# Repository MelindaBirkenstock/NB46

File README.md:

# NB47
 NB47 Mechanical keyboard, supports MX
probably doesn't work no promises

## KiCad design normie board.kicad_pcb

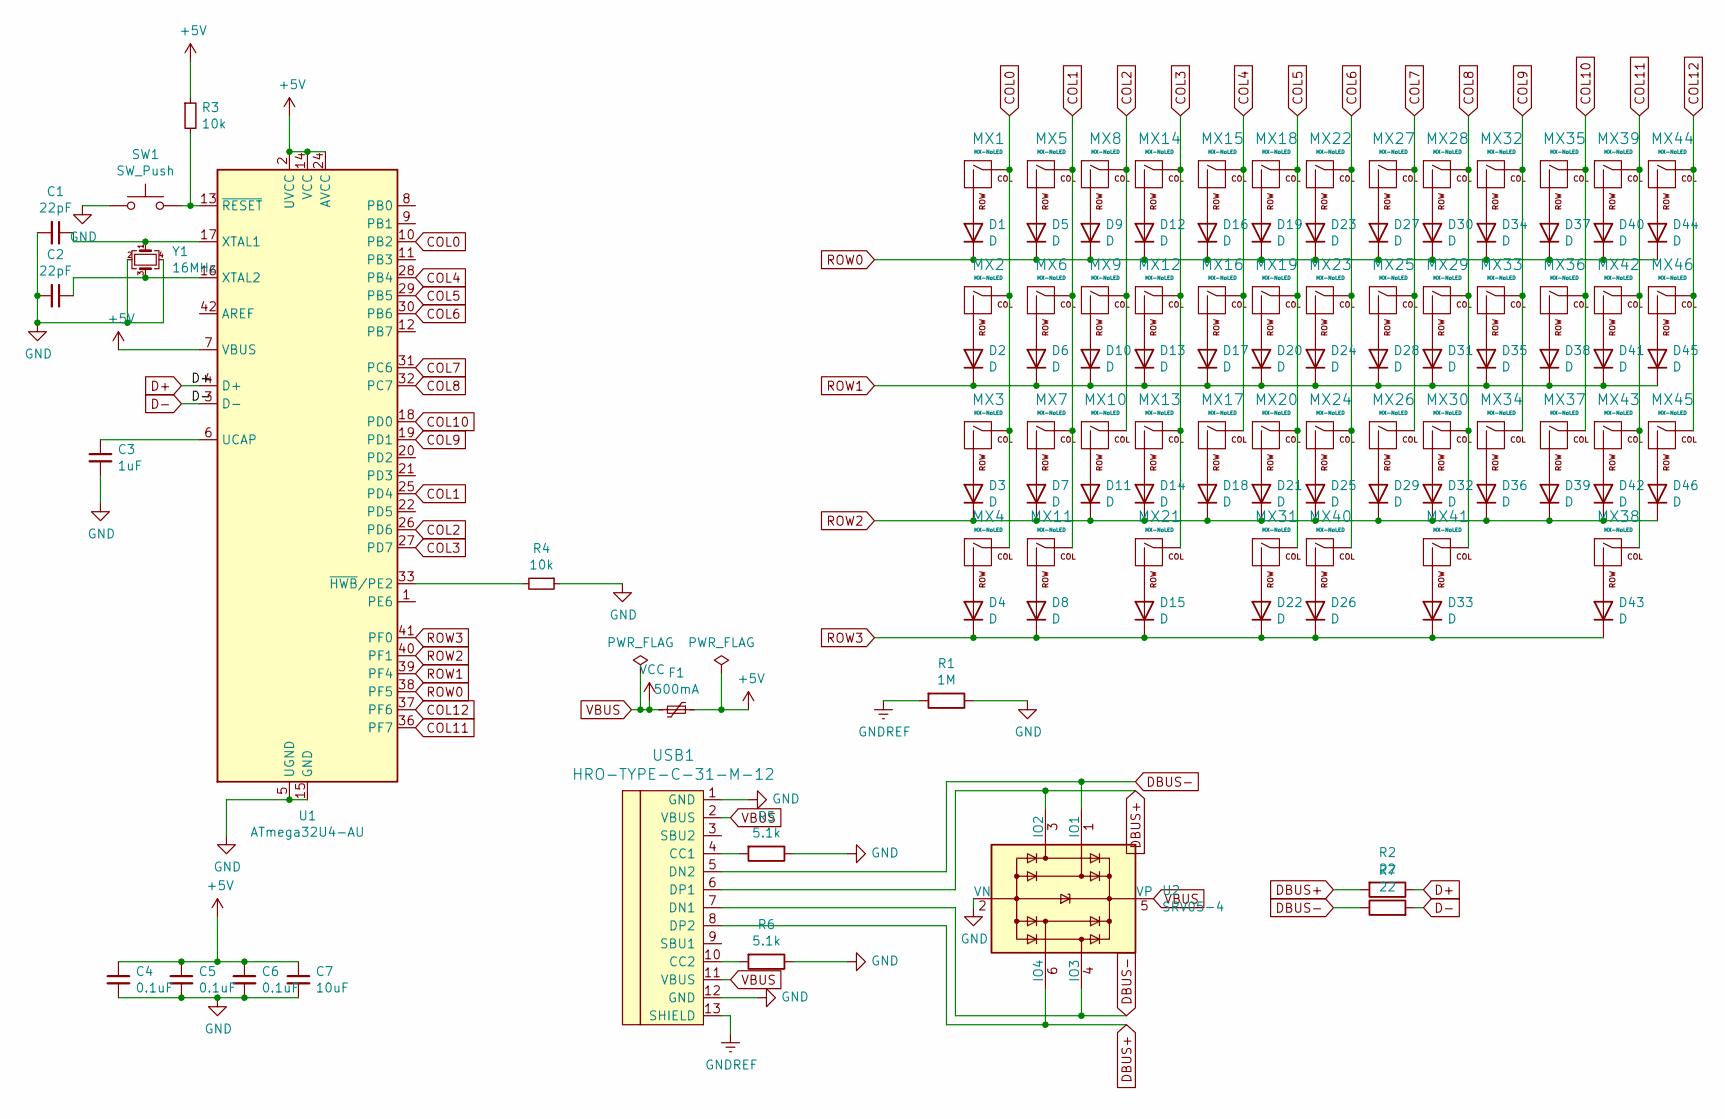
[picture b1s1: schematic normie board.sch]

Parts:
C1, C2: 22pF; C_0805_2012Metric_Pad1.15x1.40mm_HandSolder
C3: 1uF; C_0805_2012Metric_Pad1.15x1.40mm_HandSolder
C4, C5, C6: 0.1uF; C_0805_2012Metric_Pad1.15x1.40mm_HandSolder
C7: 10uF; C_0805_2012Metric_Pad1.15x1.40mm_HandSolder
D1, D2, D3, D4, D5, D6, D7, D8, D9, D10, D11, D12, D13, D14, D15, D16, D17, D18, D19, D20, D21, D22, D23, D24, D25, D26, D27, D28, D29, D30, D31, D32, D33, D34, D35, D36, D37, D38, D39, D40, D41, D42, D43, D44, D45, D46: D; D_0805_2012Metric_Pad1.15x1.40mm_HandSolder
F1: 500mA; Fuse_1206_3216Metric_Pad1.42x1.75mm_HandSolder
MX1, MX4, MX38, MX39, MX43: MX-NoLED; SW_Cherry_MX_1.50u_PCB
MX2, MX42: MX-NoLED; SW_Cherry_MX_1.75u_PCB
MX3, MX21: MX-NoLED; SW_Cherry_MX_2.25u_PCB
MX5, MX6, MX7, MX8, MX9, MX10, MX12, MX13, MX14, MX15, MX16, MX17, MX18, MX19, MX20, MX22, MX23, MX24, MX25, MX26, MX27, MX28, MX29, MX30, MX31, MX32, MX33, MX34, MX35, MX36, MX37, MX44, MX45, MX46: MX-NoLED; SW_Cherry_MX_1.00u_PCB
MX11, MX41: MX-NoLED; SW_Cherry_MX_1.25u_PCB
MX40: MX-NoLED; SW_Cherry_MX_2.75u_PCB
R1: 1M; R_0805_2012Metric_Pad1.15x1.40mm_HandSolder
R2, R7: 22; R_0805_2012Metric_Pad1.15x1.40mm_HandSolder
R3, R4: 10k; R_0805_2012Metric_Pad1.15x1.40mm_HandSolder
R5, R6: 5.1k; R_0805_2012Metric_Pad1.15x1.40mm_HandSolder
SW1: SW_Push; PinHeader_1x02_P2.54mm_Horizontal
U1: ATmega32U4-AU; TQFP-44_10x10mm_P0.8mm
U2: SRV05-4; SOT-23-6
USB1: HRO-TYPE-C-31-M-12; HRO-TYPE-C-31-M-12-HandSoldering
Y1: 16MHz; Crystal_SMD_3225-4Pin_3.2x2.5mm

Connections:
+5V: C4.1, C5.1, C6.1, C7.1, F1.1, R3.1, U1.2 (UVCC), U1.7 (VBUS), U1.14 (VCC), U1.24 (AVCC), U1.34 (VCC), U1.44 (AVCC)
COL0: MX1.1 (COL), MX2.1 (COL), MX3.1 (COL), MX4.1 (COL), U1.10 (PB2)
COL1: MX5.1 (COL), MX6.1 (COL), MX7.1 (COL), MX11.1 (COL), U1.25 (PD4)
COL2: MX8.1 (COL), MX9.1 (COL), MX10.1 (COL), U1.26 (PD6)
COL3: MX12.1 (COL), MX13.1 (COL), MX14.1 (COL), MX21.1 (COL), U1.27 (PD7)
COL4: MX15.1 (COL), MX16.1 (COL), MX17.1 (COL), U1.28 (PB4)
COL5: MX18.1 (COL), MX19.1 (COL), MX20.1 (COL), MX31.1 (COL), U1.29 (PB5)
COL6: MX22.1 (COL), MX23.1 (COL), MX24.1 (COL), MX40.1 (COL), U1.30 (PB6)
COL7: MX25.1 (COL), MX26.1 (COL), MX27.1 (COL), U1.31 (PC6)
COL8: MX28.1 (COL), MX29.1 (COL), MX30.1 (COL), MX41.1 (COL), U1.32 (PC7)
COL9: MX32.1 (COL), MX33.1 (COL), MX34.1 (COL), U1.19 (PD1)
COL10: MX35.1 (COL), MX36.1 (COL), MX37.1 (COL), U1.18 (PD0)
COL11: MX38.1 (COL), MX39.1 (COL), MX42.1 (COL), MX43.1 (COL), U1.36 (PF7)
COL12: MX44.1 (COL), MX45.1 (COL), MX46.1 (COL), U1.37 (PF6)
D+: R2.1, U1.4 (D+)
D-: R7.2, U1.3 (D-)
DBUS+: R2.2, U2.3 (IO2), U2.6 (IO4), USB1.6 (DP1), USB1.8 (DP2)
DBUS-: R7.1, U2.1 (IO1), U2.4 (IO3), USB1.5 (DN2), USB1.7 (DN1)
GND: C1.2, C2.2, C3.2, C4.2, C5.2, C6.2, C7.2, R1.1, R4.1, R5.1, R6.1, SW1.1, U1.5 (UGND), U1.15 (GND), U1.23 (GND), U1.35 (GND), U1.43 (GND), U2.2 (VN), USB1.1 (GND), USB1.12 (GND), Y1.2, Y1.4
GNDREF: R1.2, USB1.13 (SHIELD)
unnamed: C1.1, U1.17 (XTAL1), Y1.1
unnamed: C2.1, U1.16 (XTAL2), Y1.3
unnamed: C3.1, U1.6 (UCAP)
unnamed: D1.2 (A), MX1.2 (ROW)
unnamed: D2.2 (A), MX2.2 (ROW)
unnamed: D3.2 (A), MX3.2 (ROW)
unnamed: D4.2 (A), MX4.2 (ROW)
unnamed: D5.2 (A), MX5.2 (ROW)
unnamed: D6.2 (A), MX6.2 (ROW)
unnamed: D7.2 (A), MX7.2 (ROW)
unnamed: D8.2 (A), MX11.2 (ROW)
unnamed: D9.2 (A), MX8.2 (ROW)
unnamed: D10.2 (A), MX9.2 (ROW)
unnamed: D11.2 (A), MX10.2 (ROW)
unnamed: D12.2 (A), MX14.2 (ROW)
unnamed: D13.2 (A), MX12.2 (ROW)
unnamed: D14.2 (A), MX13.2 (ROW)
unnamed: D15.2 (A), MX21.2 (ROW)
unnamed: D16.2 (A), MX15.2 (ROW)
unnamed: D17.2 (A), MX16.2 (ROW)
unnamed: D18.2 (A), MX17.2 (ROW)
unnamed: D19.2 (A), MX18.2 (ROW)
unnamed: D20.2 (A), MX19.2 (ROW)
unnamed: D21.2 (A), MX20.2 (ROW)
unnamed: D22.2 (A), MX31.2 (ROW)
unnamed: D23.2 (A), MX22.2 (ROW)
unnamed: D24.2 (A), MX23.2 (ROW)
unnamed: D25.2 (A), MX24.2 (ROW)
unnamed: D26.2 (A), MX40.2 (ROW)
unnamed: D27.2 (A), MX27.2 (ROW)
unnamed: D28.2 (A), MX25.2 (ROW)
unnamed: D29.2 (A), MX26.2 (ROW)
unnamed: D30.2 (A), MX28.2 (ROW)
unnamed: D31.2 (A), MX29.2 (ROW)
unnamed: D32.2 (A), MX30.2 (ROW)
unnamed: D33.2 (A), MX41.2 (ROW)
unnamed: D34.2 (A), MX32.2 (ROW)
unnamed: D35.2 (A), MX33.2 (ROW)
unnamed: D36.2 (A), MX34.2 (ROW)
unnamed: D37.2 (A), MX35.2 (ROW)
unnamed: D38.2 (A), MX36.2 (ROW)
unnamed: D39.2 (A), MX37.2 (ROW)
unnamed: D40.2 (A), MX39.2 (ROW)
unnamed: D41.2 (A), MX42.2 (ROW)
unnamed: D42.2 (A), MX43.2 (ROW)
unnamed: D43.2 (A), MX38.2 (ROW)
unnamed: D44.2 (A), MX44.2 (ROW)
unnamed: D45.2 (A), MX46.2 (ROW)
unnamed: D46.2 (A), MX45.2 (ROW)
unnamed: R3.2, SW1.2, U1.13 (~RESET)
unnamed: R4.2, U1.33 (~HWB~/PE2)
unnamed: R5.2, USB1.4 (CC1)
unnamed: R6.2, USB1.10 (CC2)
ROW0: D1.1 (K), D5.1 (K), D9.1 (K), D12.1 (K), D16.1 (K), D19.1 (K), D23.1 (K), D27.1 (K), D30.1 (K), D34.1 (K), D37.1 (K), D40.1 (K), D44.1 (K), U1.38 (PF5)
ROW1: D2.1 (K), D6.1 (K), D10.1 (K), D13.1 (K), D17.1 (K), D20.1 (K), D24.1 (K), D28.1 (K), D31.1 (K), D35.1 (K), D38.1 (K), D41.1 (K), D45.1 (K), U1.39 (PF4)
ROW2: D3.1 (K), D7.1 (K), D11.1 (K), D14.1 (K), D18.1 (K), D21.1 (K), D25.1 (K), D29.1 (K), D32.1 (K), D36.1 (K), D39.1 (K), D42.1 (K), D46.1 (K), U1.40 (PF1)
ROW3: D4.1 (K), D8.1 (K), D15.1 (K), D22.1 (K), D26.1 (K), D33.1 (K), D43.1 (K), U1.41 (PF0)
VBUS: F1.2, U2.5 (VP), USB1.2 (VBUS), USB1.11 (VBUS)

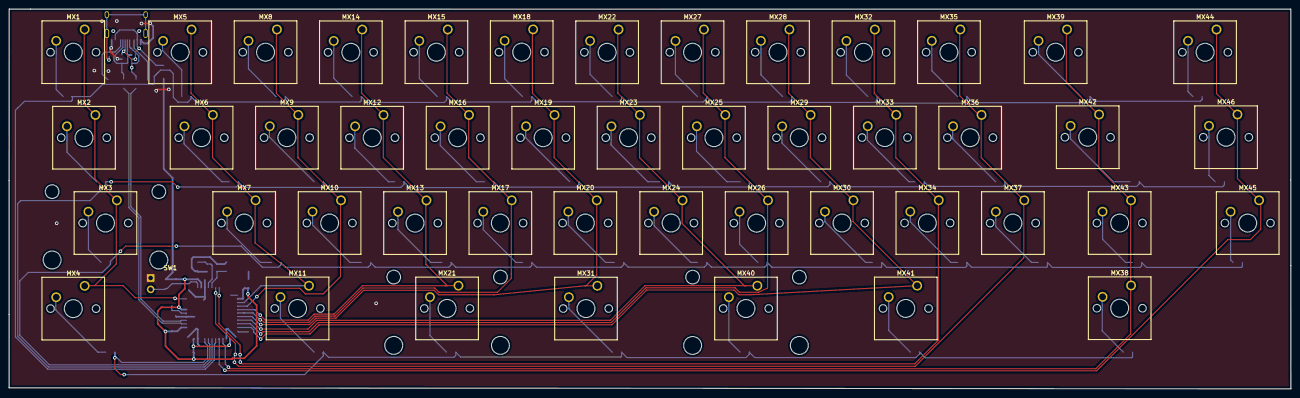
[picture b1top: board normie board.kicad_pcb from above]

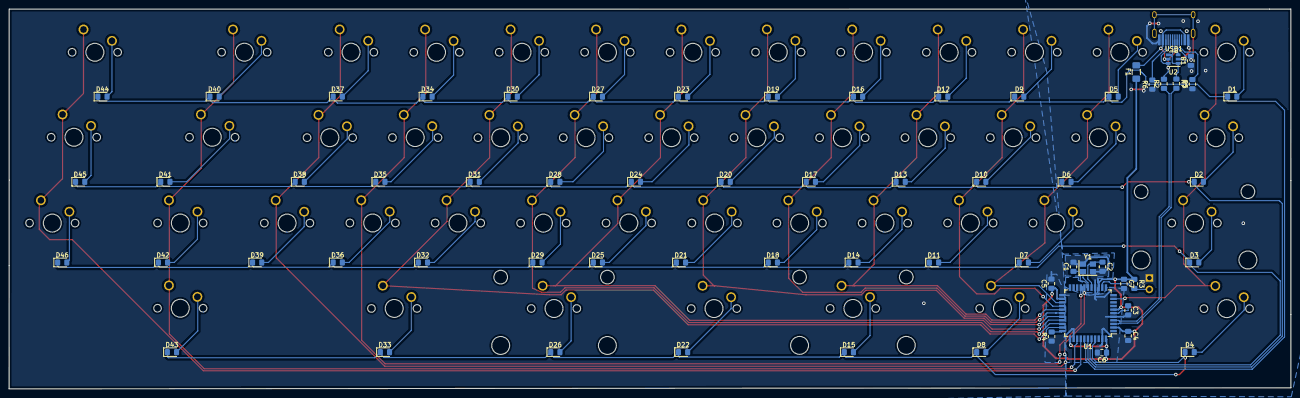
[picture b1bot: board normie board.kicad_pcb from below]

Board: 2 copper layers, 285.9 x 84.7 mm, 112 parts (65 on the bottom side), 78 nets.

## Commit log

2020-07-18 First semi-completed push of NB46
    Entire board is completed and routed, all that is left is the ground plane and art, barring no issues with the routing or footprints.
2020-07-18 NB46
    Added a ground plane, and fixed all the disconnected traces, on paper it should work
2020-07-19 rev whatever
    Updated NB to have 19.05 spacing, and rearranged some trices
